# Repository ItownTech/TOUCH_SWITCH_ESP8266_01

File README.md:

# TOUCH SWITCH ESP8266-01
Projecto em PROGRESSO completo com PCB e Código para um SWITCH Touch utilizando um ESP8266 01, e uma fonte de alimentação 220v para 3.3V

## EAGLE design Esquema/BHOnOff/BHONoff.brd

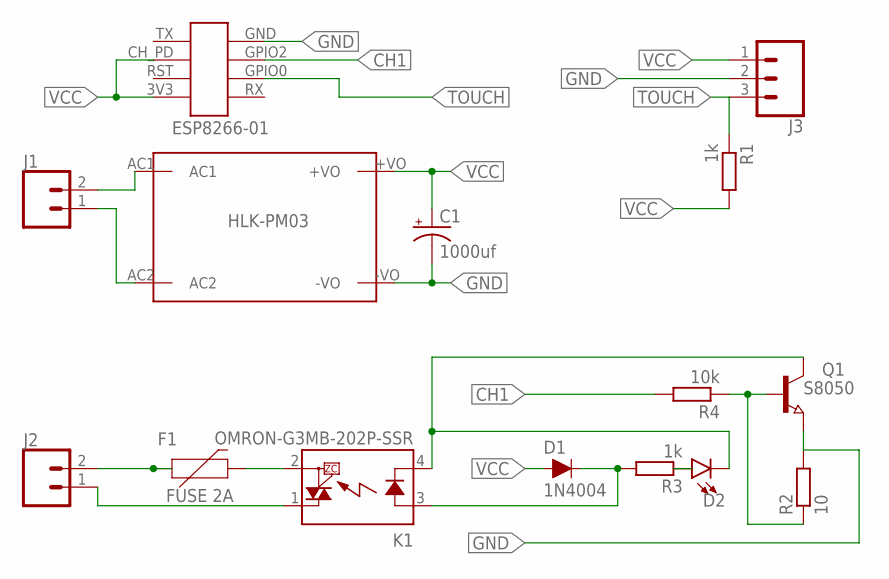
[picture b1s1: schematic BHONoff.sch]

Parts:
C1: 1000uf; 140CLH-1010
D1: 1N4004; SOD-323
D2: LED0603; LED-0603
F1: FUSE 2A; PTH
J1, J2: CONN_025MM; SCREWTERMINAL-5MM-2
J3: CONN_03; 1X03
K1: OMRON-G3MB-202P-SSR
Q1: S8050; SOT23
R1, R3: 1k; R0603
R2: 10; R0603
R4: 10k; R0603
U$2: HLK-PM03
U$3: ESP8266-01

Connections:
CH1: R4.2, U$3.GPIO2
GND: C1.-, J3.2, Q1.2 (E), R2.2, U$2.-VO, U$3.GND
unnamed: D2.C, K1.4 (K), Q1.3 (C)
unnamed: J2.1, K1.1 (DS1)
unnamed: Q1.1 (B), R2.1, R4.1
unnamed: F1.P$1 (1), J2.2
unnamed: J1.2, U$2.AC1
unnamed: J1.1, U$2.AC2
unnamed: F1.P$2 (2), K1.2 (DS2)
unnamed: D1.C, K1.3 (A), R3.2
unnamed: D2.A, R3.1
TOUCH: J3.3, R1.1, U$3.GPIO0
VCC: C1.+, D1.A, J3.1, R1.2, U$2.+VO, U$3.3V3, U$3.CH_PD

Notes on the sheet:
HLK-PM03
ESP8266-01

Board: 2 copper layers, 15 parts (0 on the bottom side), 13 nets, no tracks yet.

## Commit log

2017-09-26 Esquema eagle, PCB em desenvolvimento

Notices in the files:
parts and their libraries:
SparkFun-Connectors: Licensing: Creative Commons ShareAlike 4.0 International - https://creativecommons.org/licenses/by-sa/4.0
